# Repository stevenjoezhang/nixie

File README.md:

# Nixie

## Hardware

- [Arduino Mega 2560](https://store.arduino.cc/products/arduino-mega-2560-rev3)
- [IN-14 Nixie tube](https://en.wikipedia.org/wiki/Nixie_tube)
- [DS3231](https://www.maximintegrated.com/en/products/analog/real-time-clocks/DS3231.html)

## Software Dependencies

- [Rtc](https://github.com/Makuna/Rtc)
- [SoftwareWire](https://github.com/Testato/SoftwareWire)

## Related Work

- [NixieTubeClock](https://github.com/zer0pwned/NixieTubeClock)

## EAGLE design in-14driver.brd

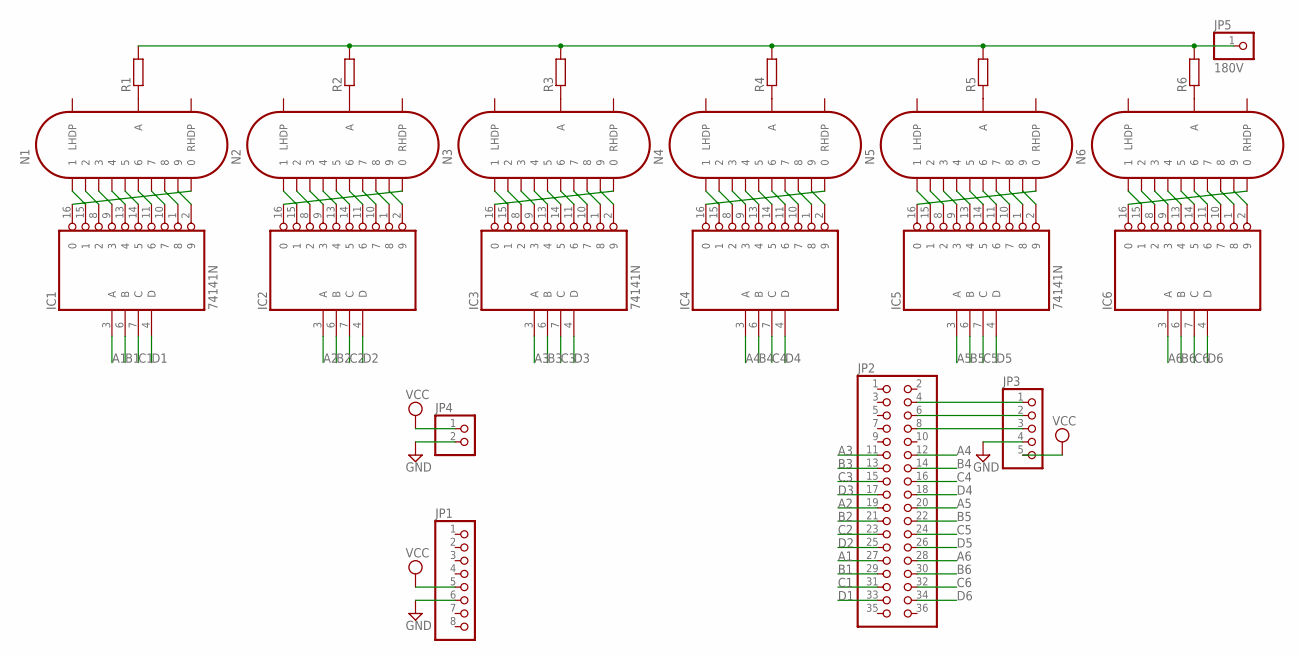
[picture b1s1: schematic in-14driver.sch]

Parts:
IC1, IC2, IC3, IC4, IC5, IC6: 74141N; DIL16
JP1: PINHD-1X8; 1X08
JP2: PINHD-2X18; 2X18
JP3: PINHD-1X5; 1X05
JP4: PINHD-1X2; 1X02
JP5: 180V; 1X01
N1, N2, N3, N4, N5, N6: IN-14
R1, R2, R3, R4, R5, R6: R-EU_0207/10; 0207/10

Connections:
A1: IC1.3 (A), JP2.27
A2: IC2.3 (A), JP2.19
A3: IC3.3 (A), JP2.11
A4: IC4.3 (A), JP2.12
A5: IC5.3 (A), JP2.20
A6: IC6.3 (A), JP2.28
B1: IC1.6 (B), JP2.29
B2: IC2.6 (B), JP2.21
B3: IC3.6 (B), JP2.13
B4: IC4.6 (B), JP2.14
B5: IC5.6 (B), JP2.22
B6: IC6.6 (B), JP2.30
C1: IC1.7 (C), JP2.31
C2: IC2.7 (C), JP2.23
C3: IC3.7 (C), JP2.15
C4: IC4.7 (C), JP2.16
C5: IC5.7 (C), JP2.24
C6: IC6.7 (C), JP2.32
D1: IC1.4 (D), JP2.33
D2: IC2.4 (D), JP2.25
D3: IC3.4 (D), JP2.17
D4: IC4.4 (D), JP2.18
D5: IC5.4 (D), JP2.26
D6: IC6.4 (D), JP2.34
GND: IC1.12 (GND), IC2.12 (GND), IC3.12 (GND), IC4.12 (GND), IC5.12 (GND), IC6.12 (GND), JP1.6, JP3.4, JP4.2
unnamed: IC2.15 (1), N2.0 (1)
unnamed: IC2.8 (2), N2.9 (2)
unnamed: IC2.9 (3), N2.8 (3)
unnamed: IC2.13 (4), N2.7 (4)
unnamed: IC2.14 (5), N2.6 (5)
unnamed: IC2.11 (6), N2.5 (6)
unnamed: IC2.10 (7), N2.4 (7)
unnamed: IC2.1 (8), N2.3 (8)
unnamed: IC2.2 (9), N2.2 (9)
unnamed: IC2.16 (0), N2.1 (0)
unnamed: N2.A, R2.1
unnamed: IC3.15 (1), N3.0 (1)
unnamed: IC3.8 (2), N3.9 (2)
unnamed: IC3.9 (3), N3.8 (3)
unnamed: IC3.13 (4), N3.7 (4)
unnamed: IC3.14 (5), N3.6 (5)
unnamed: IC3.11 (6), N3.5 (6)
unnamed: IC3.10 (7), N3.4 (7)
unnamed: IC3.1 (8), N3.3 (8)
unnamed: IC3.2 (9), N3.2 (9)
unnamed: JP2.4, JP3.1
unnamed: JP2.6, JP3.2
unnamed: JP2.8, JP3.3
unnamed: IC3.16 (0), N3.1 (0)
unnamed: N3.A, R3.1
unnamed: IC4.15 (1), N4.0 (1)
unnamed: IC4.8 (2), N4.9 (2)
unnamed: IC4.9 (3), N4.8 (3)
unnamed: IC4.13 (4), N4.7 (4)
unnamed: IC4.14 (5), N4.6 (5)
unnamed: IC4.11 (6), N4.5 (6)
unnamed: IC4.10 (7), N4.4 (7)
unnamed: IC4.1 (8), N4.3 (8)
unnamed: IC4.2 (9), N4.2 (9)
unnamed: IC4.16 (0), N4.1 (0)
unnamed: N4.A, R4.1
unnamed: IC5.15 (1), N5.0 (1)
unnamed: IC5.8 (2), N5.9 (2)
unnamed: IC5.9 (3), N5.8 (3)
unnamed: IC5.13 (4), N5.7 (4)
unnamed: IC5.14 (5), N5.6 (5)
unnamed: IC5.11 (6), N5.5 (6)
unnamed: IC5.10 (7), N5.4 (7)
unnamed: IC1.15 (1), N1.0 (1)
unnamed: IC1.8 (2), N1.9 (2)
unnamed: IC1.9 (3), N1.8 (3)
unnamed: IC1.13 (4), N1.7 (4)
unnamed: IC1.14 (5), N1.6 (5)
unnamed: IC1.11 (6), N1.5 (6)
unnamed: IC1.10 (7), N1.4 (7)
unnamed: IC1.1 (8), N1.3 (8)
unnamed: IC1.2 (9), N1.2 (9)
unnamed: IC1.16 (0), N1.1 (0)
unnamed: IC5.1 (8), N5.3 (8)
unnamed: IC5.2 (9), N5.2 (9)
unnamed: IC5.16 (0), N5.1 (0)
unnamed: N5.A, R5.1
unnamed: IC6.15 (1), N6.0 (1)
unnamed: IC6.8 (2), N6.9 (2)
unnamed: IC6.9 (3), N6.8 (3)
unnamed: IC6.13 (4), N6.7 (4)
unnamed: IC6.14 (5), N6.6 (5)
unnamed: IC6.11 (6), N6.5 (6)
unnamed: N1.A, R1.1
unnamed: IC6.10 (7), N6.4 (7)
unnamed: IC6.1 (8), N6.3 (8)
unnamed: IC6.2 (9), N6.2 (9)
unnamed: IC6.16 (0), N6.1 (0)
unnamed: N6.A, R6.1
VCC: IC1.5 (VCC), IC2.5 (VCC), IC3.5 (VCC), IC4.5 (VCC), IC5.5 (VCC), IC6.5 (VCC), JP1.5, JP3.5, JP4.1
VH: JP5.1, R1.2, R2.2, R3.2, R4.2, R5.2, R6.2

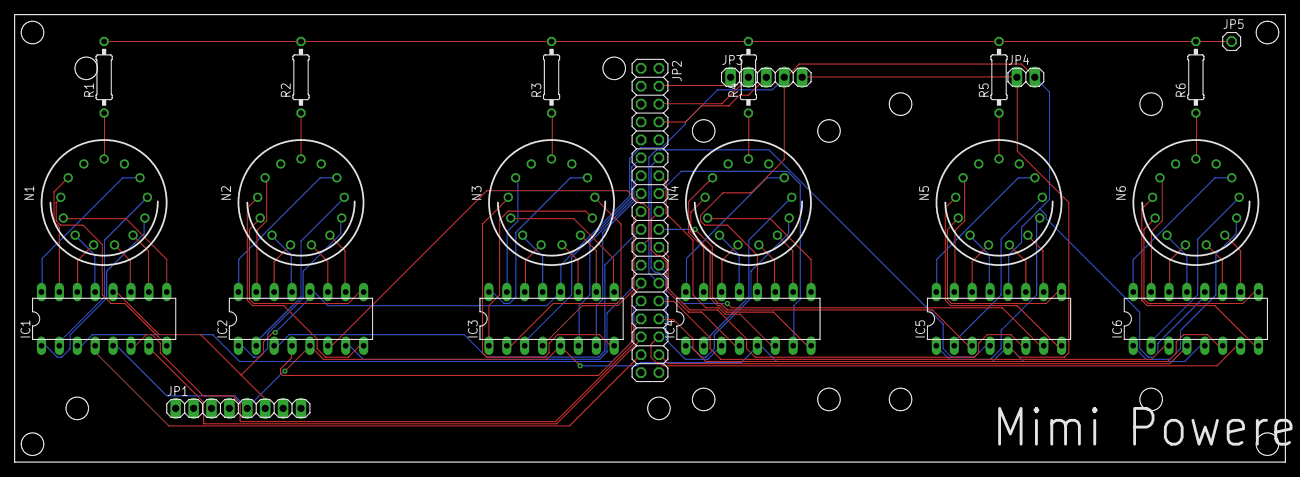
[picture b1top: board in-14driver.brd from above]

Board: 2 copper layers, 180.3 x 63.5 mm, 23 parts (0 on the bottom side), 96 nets.

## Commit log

2019-12-26 Init
2020-01-10 Create LICENSE
2021-09-21 Switch to DS3231
2021-12-27 Update pins
